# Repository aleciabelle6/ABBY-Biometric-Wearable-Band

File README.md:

# Anxiety Buddy Band for Youth (ABBY) - Biometric Wearable Band  
_Alecia Barbieri — Princeton University ECE Funded Summer Internship, 2023_

## Project Overview

This repository contains the KiCad design files for a custom Electrodermal Activity (EDA) and heart rate/blood oxygen sensor signal conditioning circuit. It integrates analog signal conditioning stages to filter, amplify, and prepare the weak physiological signals from wearable electrodes and sensors for digitization. This project involved extending and enhancing the Open-Smartwatch-Light open-source platform (https://open-smartwatch.github.io/) by advancing its electronic hardware and serves as my first exposure to KiCAD. 

The circuit is designed to amplify and clean signals from EDA electrodes, with additional capability for heart rate and blood oxygen sensing and position tracking. The design focuses on maximizing signal fidelity through multi-stage amplification and filtering, using a low-power LM324D operational amplifier.

---

## Circuit Extension Design Summary

Taking on this project with no prior experience in PCB design was a very daunting but nonetheless rewarding endeavor. As such, I gained so much knowledge from starting with an open-source PCB layout and extending the functionality of it. Below, I describe the various additions that I made to the design.

### Heart rate and Pulse Sensing

The BH1792GLC-E2 is an optical sensor that measures heart rate and pulse by detecting changes in blood volume using reflected green light. It emits green light through integrated LEDs and captures the reflected signal from skin tissue using a photodiode. This reflected light varies with blood flow, allowing the sensor to extract photoplethysmography (PPG) pulse wave information that is digitized internally and outputt via I2C to the ESP32 microcontroller. The sensor operates with precise timing control and built-in ambient light cancellation for the purpose of enhancing signal quality and reducing noise.

### EDA Sensor Signal Processing

EDA (Electrodermal Activity) electrodes measure changes in skin conductance caused by sweat gland activity, which reflects stress levels. I designed an analog signal conditioning chain that consists of three distinct stages, each implemented using one of the four internal amplifiers in the LM324D quad op-amp IC, for the purpose of having access to noise-free, clear, and useful data that can inform the microcontroller on parts of the physiological makeup that even the user isn't aren't aware of. The raw EDA signal interfaces with the board through an SJ-3524 connector. From there it gets processed through a 3-stage amplifier. The first stage is a differential amplifier stage, which takes in the raw EDA electrode signals, biased with a 1.65 V reference to accommodate single-supply operation and amplifies the differential signal from the electrodes while rejecting common-mode noise and interference. The second stage is an active low-pass filter stage which attenuates high-frequency noise and artifacts, preserving the low-frequency physiological signals typical in EDA and heart rate sensing. The third and final stage is the gain stage, which provides a gain of 11 to bring the signal into an optimal range for analog-to-digital conversion. This conditioned final signal then gets sent to an ADC input that then interfaces with the I2C protocols of the ESP32 at address 0x48.  

### Miscellaneous Changes
I changed the circular Open-Smartwatch-Light into a rectangular board to have enough room to accommodate the new devices. With this, I rerouted the entire board, prioritizing sectioning off analog, digital, and power lines as much as possible with the limited board space and also prioritized having sufficient trace width for the current passing through each branch of the circuit. 

---

## Circuit Component Overview

This section highlights the different components' functions in the circuit as visually depicted in the image below.

The TTGO T-Micro32 V2.0 (ESP32-based Microcontroller) was used due to its very compact size, coming in at 45% smaller than standard ESP32. It has full GPIO support, Wi-Fi and Bluetooth features, and advanced power-saving features including clock gating, deep sleep, and dynamic power delegation. This microcontroller controls all of the devices, primarily using I2C to communicate with the different sensors as well as the ADC converter.

As far as sensing, the BH1792GLC-E2 ECG/PPG Heart Rate and Oximeter Sensor is an IR-based pulse wave sensor for heart rate and SpO2 monitoring. Communicates via I2C, uses interrupt-based burst reads, and includes bypass capacitors for power stability. The BMA400 3-axis accelerometer is an ultra-low power accelerometer for motion and activity tracking. It integrates with I2C, uses INT pin for data-ready alerts, and includes bypass capacitor for voltage filtering. The board supports an external pair of EDA electrodes spaced 4 cm apart at the top and bottom of the wrist for optimal skin conductance sensing. They are routed through SJ-3524 connector, then through 3-stage amplifier, then through ADC, then to I2C. In order for the EDA electrodes to be able to interface with the rest of the electronics, it must have a SJ-3524-SMT connector jack as seen in this pair of EDA electrodes: https://lafayettepolygraph.com/products/eda-assembly-7ft-lx6/. Throughout the board there are many capacitors used for voltage stability, filtering, and transient suppression across biosensors, power supply, and signal lines. Resistors are also employed in various places for pulling up the I2C lines as well as noise cancelling, as seen in the low pass filter for the EDA electrode signals.

The GC9A01 IPS Display: 1.28” circular IPS LCD with SPI interface, parallel RGB support, and adjustable brightness via 2N7002 transistor switch, which happenss by adjusting current through the LEDK pin on the GC9A01 screen, which in turn adjusts the backllight brightness of the display. This display screen offers wide viewing angles and vibrant display quality. There are also 3 SPST Buttons used for power enable (EN pin control) and general-purpose user inputs (e.g. calibrate, transmit).

The power delegation of the board is quite intuitive. The board is powered by a 3.7V LiPo battery with shorting protection; monitored via voltage divider and B_MON pin for on-screen battery status display. The MCP73831 LiPo Charging Management Controller is a constant-current/voltage charger with thermal regulation, charge termination, and USB-powered battery input for safe, efficient battery management. The TPS2115A Power Multiplexer is a smart autoswitching between USB and battery power sources based on availability and voltage conditions. It acts very similiar to a rely in that it relies on the battery level of the battery to determine which input to transfer to the output and to the next stage of the power management system. The PCB also contains 2 XC6209 LDO Voltage regulators that convert the output of the multiplexer to a consistent 3.3V output regardless of the input level, allowing for consistent operation of sensor powering and the main logic throughout the circuit. The micro-USB port has two functions as it takes in a charging cable to charge the onboard Li-Po battery using a regulated charging circuit, and this port also provides a data interface for uploading firmware to the microcontroller. This enables both power management and programming through a single, convenient connection. With this, the CH340E chip is a USB to Serial Converter converts the inputs of the micro-USB to UART to connect with the microcontroller to upload firmware. 

---

## PCB Circuit Layout Images

Below is the 3D circuit layout of the board followed by the front and back viewport as well as a 3D isometric viewport. As seen from the images below, the front of the board hosts the sensors, processors, buttons, external wire inputs, and passive components that sit on the side of the wrist in order to allow for the heart rate/pulse sensor to be able to better interface with the wrist. The back of the PCB contains the interfaces for the screen display and the external 3.7 LiPo battery, which is hosted below the screen but above the PCB.

---

## Repository Contents

- **KiCad Project Files:** Schematic, PCB layout, and BOM files for the full EDA signal conditioning circuit.
- **EDA Models:** The symbol, footprint, and 3D CAD model for each component on the PCB.
- **Datasheets:** Relevant datasheets for each component.

## Getting Started

1. Clone the repository:
   ```bash
   git clone https://github.com/aleciabelle6/ABBY-Biometric-Wearable-Band.git
   cd ABBY-Biometric-Wearable-Band
2. On KiCAD, select **File > Open Project**.
3. Navigate to where you cloned this repository and open the file *abbyWatchV1.kicad_pro*. 

## License

This project is made available for academic, non-commercial use. Please contact me if you'd like to use any part of the content or code beyond that scope.

---
*Author: Alecia Barbieri ([LinkedIn](https://www.linkedin.com/in/aleciabarbieri))*  
*Project Advisor: Dr. David Wentzlaff*  
*Department of Electrical and Computer Engineering, Princeton University*

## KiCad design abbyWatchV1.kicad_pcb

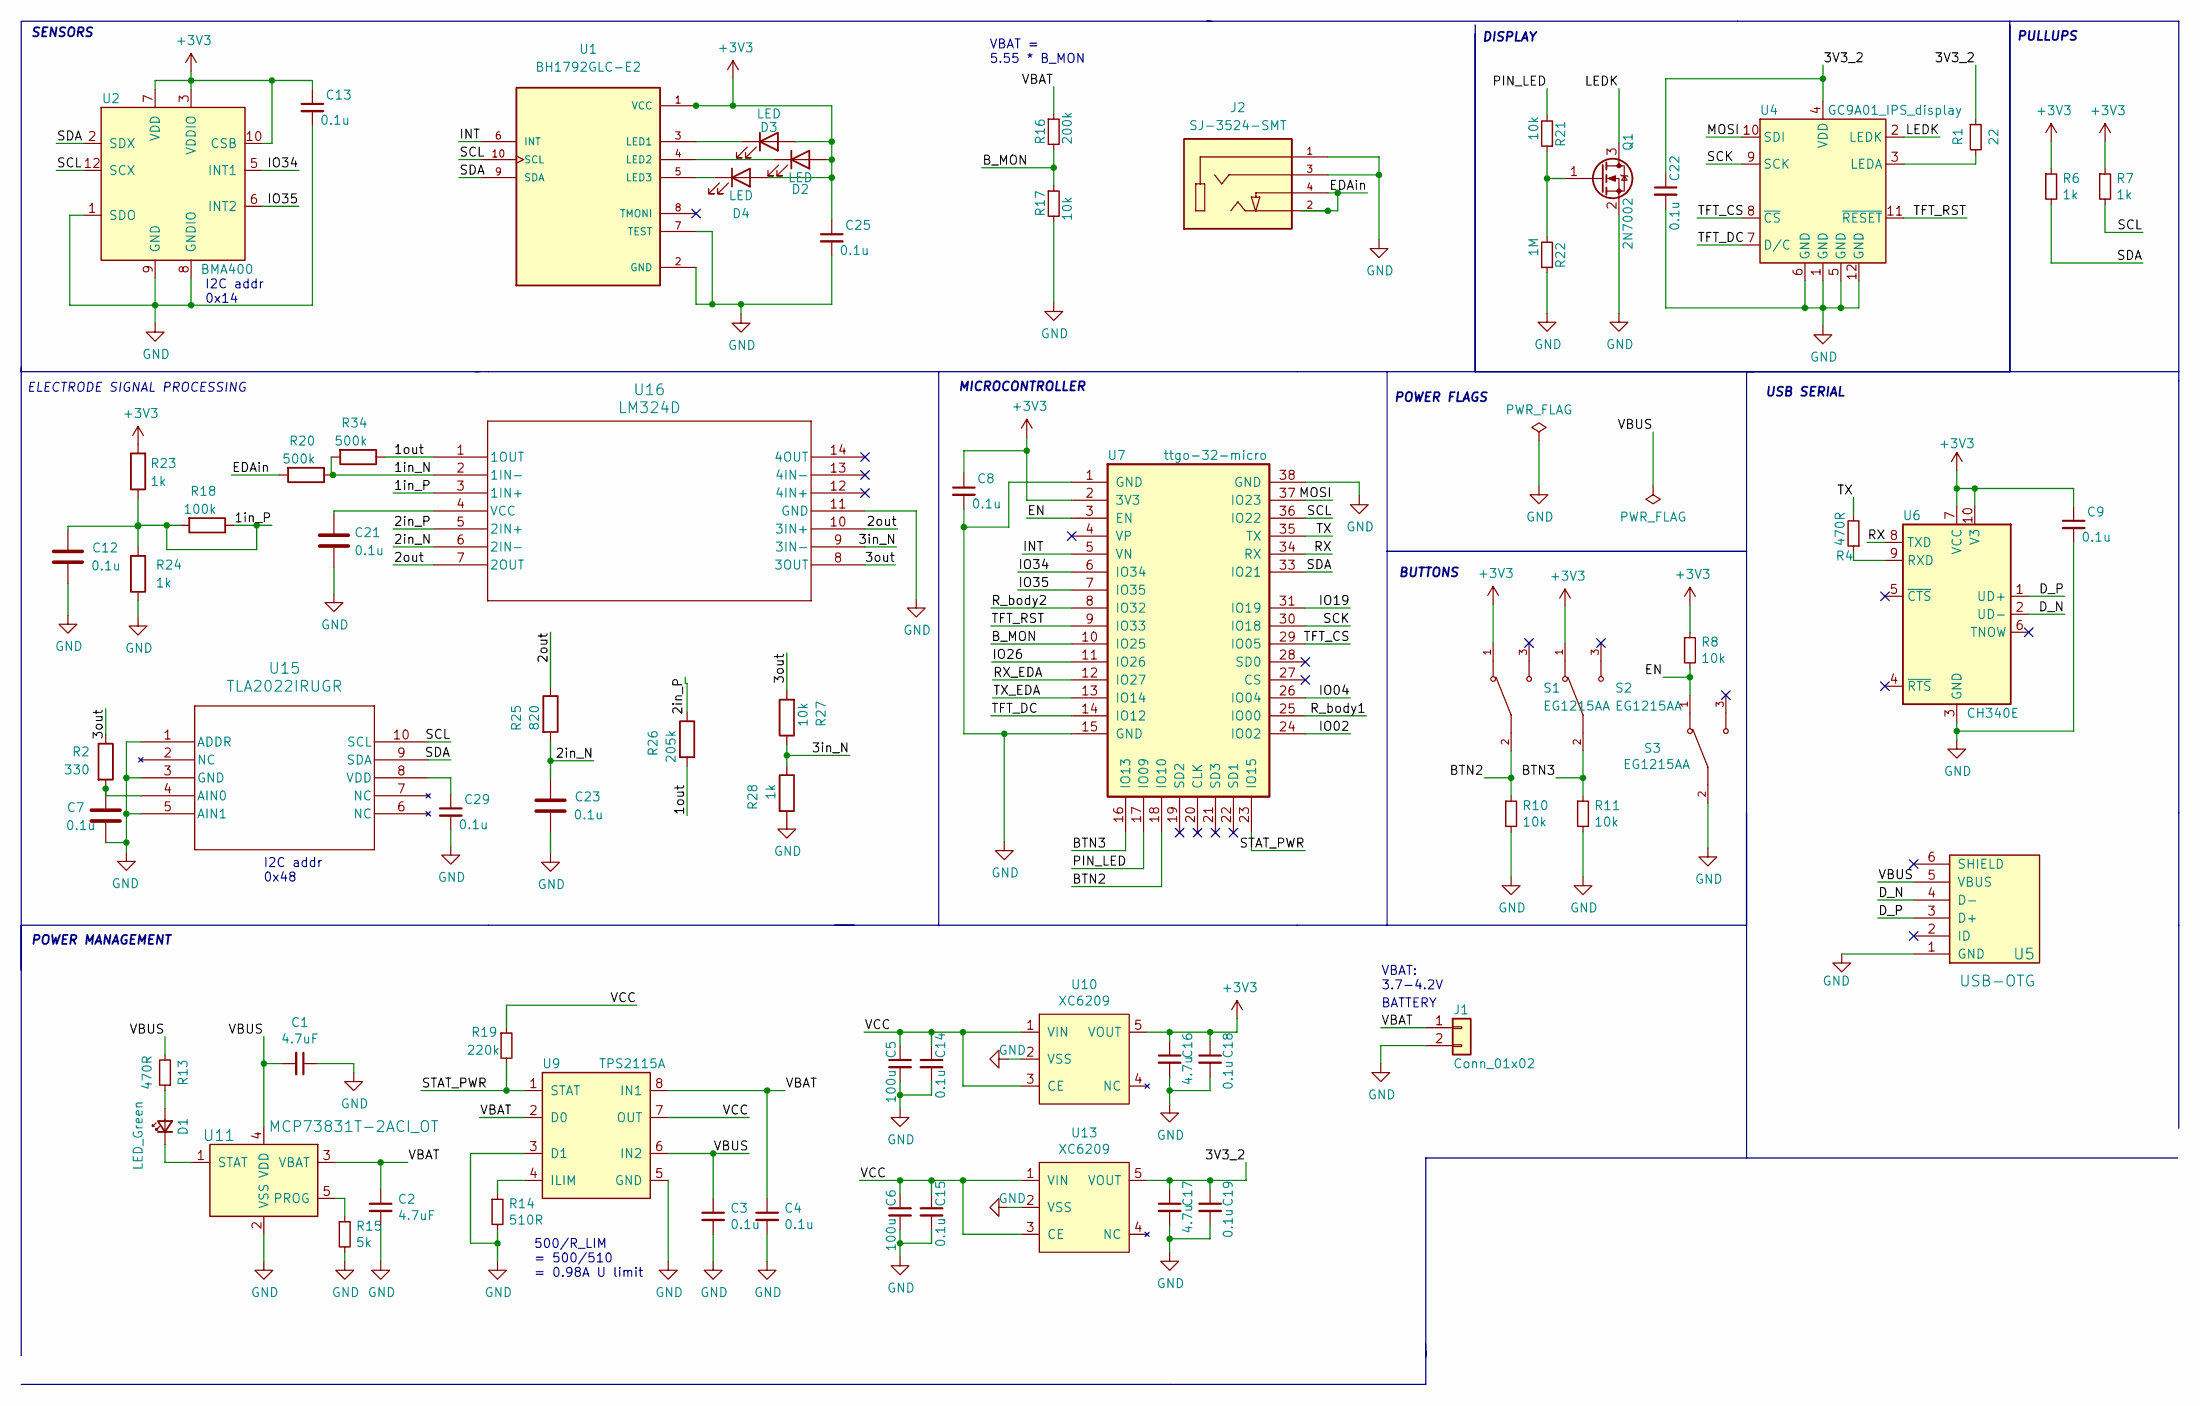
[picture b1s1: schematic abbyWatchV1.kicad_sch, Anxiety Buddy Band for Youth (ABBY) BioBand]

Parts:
C1, C2: 4.7uF; C_0603_1608Metric
C3, C4, C7, C8, C9, C12, C13, C14, C15, C18, C19, C21, C22, C23, C25, C29: 0.1u; C_0603_1608Metric
C5, C6: 100u; C_1206_3216Metric
C16, C17: 4.7u; C_0603_1608Metric
D1: LED_Green; LED_0805_2012Metric
D2, D3, D4: LED; LED_1206_3216Metric
J1: Conn_01x02; PinHeader_1x02_P2.54mm_Vertical
J2: SJ-3524-SMT; CUI_SJ-3524-SMT; PARTREV 1.03
Q1: 2N7002; SOT-23
R1: 22; R_0603_1608Metric
R2: 330; R_0603_1608Metric
R4, R13: 470R; R_0603_1608Metric
R6, R7, R23, R24, R28: 1k; R_0603_1608Metric
R8, R10, R11, R17, R21, R27: 10k; R_0603_1608Metric
R14: 510R; R_0603_1608Metric
R15: 5k; R_0603_1608Metric
R16: 200k; R_0603_1608Metric
R18: 100k; R_0603_1608Metric
R19: 220k; R_0603_1608Metric
R20, R34: 500k; R_0603_1608Metric
R22: 1M; R_0603_1608Metric
R25: 820; R_0603_1608Metric
R26: 205k; R_0603_1608Metric
S1, S2, S3: EG1215AA; CONN3_3033816_WRE; PARTREV A
U1: BH1792GLC-E2; XDCR_BH1792GLC-E2; PARTREV 002
U2: BMA400; narrow0.19mmV2BMA400; MPN BMA400; DigiKey_PN 828-1081-1-ND
U4: GC9A01_IPS_display
U5: USB-OTG; USBmicro-B
U6: CH340E; MSOP-10_3x3mm_P0.5mm
U7: ttgo-32-micro
U9: TPS2115A; TSSOP-8_4.4x3mm_P0.65mm; MPN TPS2115APWR; DigiKey_PN 296-16940-1-ND
U10, U13: XC6209; SOT-23-5
U11: MCP73831T-2ACI_OT; SOT-23-5; MPN MCP73831T-2ACI/OT; Digi-Key_PN MCP73831T-2ACI/OTCT-ND
U15: TLA2022IRUGR; RUG10_TEX
U16: LM324D; D14

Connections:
+3V3: C8.1, C9.1, C13.1, C16.1, C18.1, C25.1, D2.2 (A), D3.2 (A), D4.2 (A), R6.1, R7.1, R8.1, R23.2, S1.1, S2.1, U1.1 (VCC), U2.3 (VDDIO), U2.7 (VDD), U2.10 (CSB), U6.7 (VCC), U6.10 (V3), U7.2 (3V3), U10.5 (VOUT)
/1in_N: R20.1, R34.2, U16.2 (1IN-)
/1in_P: C12.1, R18.1, R18.2, R23.1, R24.2, U16.3 (1IN+)
/1out: R26.2, R34.1, U16.1 (1OUT)
/2in_N: C23.1, R25.2, U16.6 (2IN-)
/2in_P: R26.1, U16.5 (2IN+)
/2out: R25.1, U16.7 (2OUT), U16.10 (3IN+)
/3V3_2: C17.1, C19.1, C22.1, R1.1, U4.4 (VDD), U13.5 (VOUT)
/3in_N: R27.1, R28.1, U16.9 (3IN-)
/3out: R2.1, R27.2, U16.8 (3OUT)
/BTN2: R10.1, S1.2, U7.18 (IO10)
/BTN3: R11.1, S2.2, U7.16 (IO13)
/B_MON: R16.2, R17.1, U7.10 (IO25)
/D_N: U5.4 (D-), U6.2 (UD-)
/D_P: U5.3 (D+), U6.1 (UD+)
/EDAin: J2.2, J2.4, R20.2
/EN: R8.2, S3.1, U7.3 (EN)
/INT: U1.6 (INT), U7.5 (VN)
/IO02: U7.24 (IO02)
/IO04: U7.26 (IO04)
/IO19: U7.31 (IO19)
/IO26: U7.11 (IO26)
/IO34: U2.5 (INT1), U7.6 (IO34)
/IO35: U2.6 (INT2), U7.7 (IO35)
/LEDK: Q1.3 (D), U4.2 (LEDK)
/MOSI: U4.10 (SDI), U7.37 (IO23)
/PIN_LED: R21.2, U7.17 (IO09)
/RX: U6.8 (TXD), U7.34 (RX)
/RX_EDA: U7.12 (IO27)
/R_body1: U7.25 (IO00)
/R_body2: U7.8 (IO32)
/SCK: U4.9 (SCK), U7.30 (IO18)
/SCL: R7.2, U1.10 (SCL), U2.12 (SCX), U7.36 (IO22), U15.10 (SCL)
/SDA: R6.2, U1.9 (SDA), U2.2 (SDX), U7.33 (IO21), U15.9 (SDA)
/STAT_PWR: R19.2, U7.23 (IO15), U9.1 (STAT)
/TFT_CS: U4.8 (~CS), U7.29 (IO05)
/TFT_DC: U4.7 (D/C), U7.14 (IO12)
/TFT_RST: U4.11 (~RESET), U7.9 (IO33)
/TX: R4.2, U7.35 (TX)
/TX_EDA: U7.13 (IO14)
/VBAT: C2.1, C4.1, J1.1, R16.1, U9.2 (D0), U9.8 (IN1), U11.3 (VBAT)
/VBUS: C1.2, C3.1, R13.2, U5.5 (VBUS), U9.6 (IN2), U11.4 (VDD)
/VCC: C5.1, C6.1, C14.1, C15.1, R19.1, U9.7 (OUT), U10.1 (VIN), U10.3 (CE), U13.1 (VIN), U13.3 (CE)
GND: C1.1, C2.2, C3.2, C4.2, C5.2, C6.2, C7.2, C8.2, C9.2, C12.2, C13.2, C14.2, C15.2, C16.2, C17.2, C18.2, C19.2, C21.2, C22.2, C23.2, C25.2, C29.2, J1.2, J2.1, J2.3, Q1.2 (S), R10.2, R11.2, R14.2, R15.2, R17.2, R22.1, R24.1, R28.2, S3.2, U1.2 (GND), U1.7 (TEST), U2.1 (SDO), U2.8 (GNDIO), U2.9 (GND), U4.1 (GND), U4.5 (GND), U4.6 (GND), U4.12 (GND), U5.1 (GND), U6.3 (GND), U7.1 (GND), U7.15 (GND), U7.38 (GND), U9.3 (D1), U9.5 (GND), U10.2 (VSS), U11.2 (VSS), U13.2 (VSS), U15.1 (ADDR), U15.3 (GND), U15.5 (AIN1), U16.11 (GND)
unnamed: D1.2 (A), R13.1
unnamed: D1.1 (K), U11.1 (STAT)
unnamed: D2.1 (K), U1.4 (LED2)
unnamed: D3.1 (K), U1.3 (LED1)
unnamed: D4.1 (K), U1.5 (LED3)
unnamed: Q1.1 (G), R21.1, R22.2
unnamed: R1.2, U4.3 (LEDA)
unnamed: R4.1, U6.9 (RXD)
unnamed: R14.1, U9.4 (ILIM)
unnamed: R15.1, U11.5 (PROG)
unnamed: C7.1, R2.2, U15.4 (AIN0)
unnamed: C29.1, U15.8 (VDD)
unnamed: C21.1, U16.4 (VCC)

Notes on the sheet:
500/R_LIM = 500/510 = 0.98A U limit
VBAT = 5.55 * B_MON
I2C addr 0x14
SENSORS
POWER FLAGS
PULLUPS
ELECTRODE SIGNAL PROCESSING
BATTERY
USB SERIAL
BUTTONS
VBAT: 3.7-4.2V
MICROCONTROLLER
POWER MANAGEMENT
I2C addr 0x48
DISPLAY

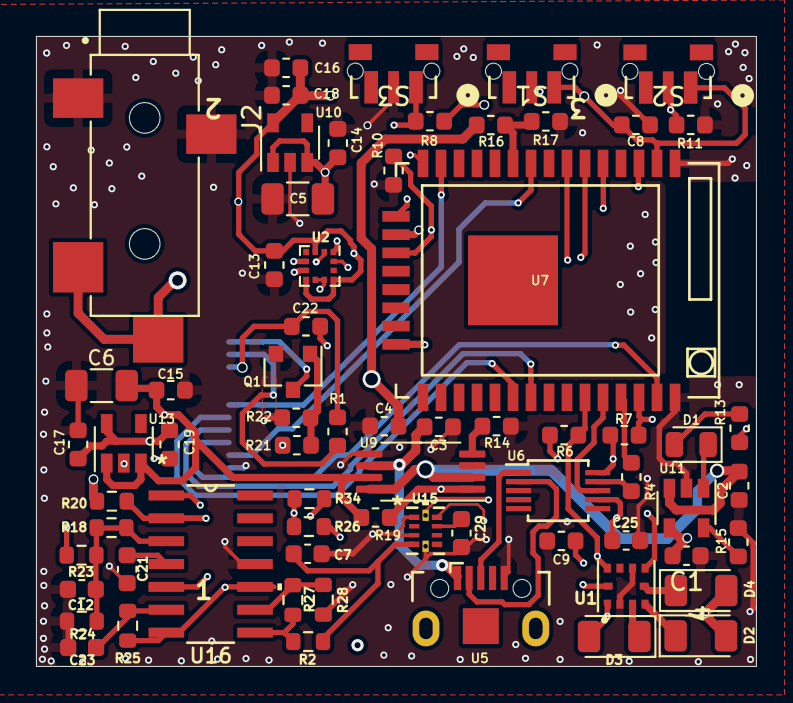
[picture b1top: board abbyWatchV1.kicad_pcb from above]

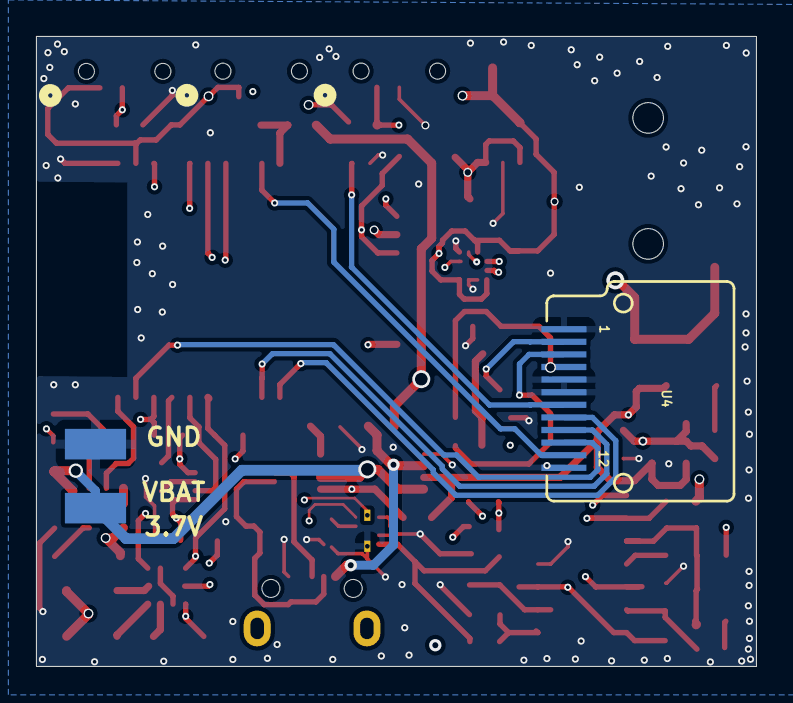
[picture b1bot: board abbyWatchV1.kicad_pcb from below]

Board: 4 copper layers, 40.0 x 35.0 mm, 69 parts (2 on the bottom side), 49 nets.

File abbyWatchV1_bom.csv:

Tool:,Eeschema 7.0.9,,,,,,,
Generator:,C:\Users\aleci\OneDrive\bin\scripting\plugins/bom_csv_grouped_by_value.py,,,,,,,
Component Count:,69,,,,,,,
,,,,,,,,
Collated Components:,,,,,,,,
,,,,,,,,
Item,Qty,Reference(s),Value,LibPart,Footprint,Datasheet,MPN,Manufacturer
1,2,"C1, C2",4.7uF,Device:C_Small,Capacitor_SMD:C_0603_1608Metric,General,General,General
2,12,"C3, C4, C8, C9, C13, C14, C15, C18, C19, C22, C25, C29",0.1u,Device:C_Small,Capacitor_SMD:C_0603_1608Metric,General,General,General
3,2,"C5, C6",100u,Device:C_Small,Capacitor_SMD:C_1206_3216Metric,General,General,General
4,4,"C7, C12, C21, C23",0.1u,Device:C,Capacitor_SMD:C_0603_1608Metric,General,General,General
5,2,"C16, C17",4.7u,Device:C_Small,Capacitor_SMD:C_0603_1608Metric,General,General,General
6,1,D1,LED_Green,Device:LED_Small,LED_SMD:LED_0805_2012Metric,General,General,General
7,3,"D2, D3, D4",LED,Device:LED,LED_SMD:LED_1206_3216Metric,General,General,General
8,1,J1,Conn_01x02,Connector_Generic:Conn_01x02,Connector_PinHeader_2.54mm:PinHeader_1x02_P2.54mm_Vertical,General,General,General
9,1,J2,SJ-3524-SMT,SJ3524:SJ-3524-SMT,SJ3524:CUI_SJ-3524-SMT,https://www.sameskydevices.com/product/resource/sj-352x-smt.pdf,SJ-352X-SMT,same sky
10,1,Q1,2N7002,Transistor_FET:2N7002,Package_TO_SOT_SMD:SOT-23,https://www.fairchildsemi.com/datasheets/2N/2N7002.pdf,,onsemi
11,1,R1,22,Device:R_Small,Resistor_SMD:R_0603_1608Metric,General,General,General
12,1,R2,330,Device:R,Resistor_SMD:R_0603_1608Metric,General,General,General
13,2,"R4, R13",470R,Device:R_Small,Resistor_SMD:R_0603_1608Metric,General,General,General
14,2,"R6, R7",1k,Device:R_Small,Resistor_SMD:R_0603_1608Metric,General,General,General
15,5,"R8, R10, R11, R17, R21",10k,Device:R_Small,Resistor_SMD:R_0603_1608Metric,General,General,General
16,1,R14,510R,Device:R_Small,Resistor_SMD:R_0603_1608Metric,General,General,General
17,1,R15,5k,Device:R_Small,Resistor_SMD:R_0603_1608Metric,General,General,General
18,1,R16,200k,Device:R_Small,Resistor_SMD:R_0603_1608Metric,General,General,General
19,1,R18,100k,Device:R,Resistor_SMD:R_0603_1608Metric,General,General,General
20,1,R19,220k,Device:R_Small,Resistor_SMD:R_0603_1608Metric,General,General,General
21,2,"R20, R34",500k,Device:R,Resistor_SMD:R_0603_1608Metric,General,General,General
22,1,R22,1M,Device:R_Small,Resistor_SMD:R_0603_1608Metric,General,General,General
23,3,"R23, R24, R28",1k,Device:R,Resistor_SMD:R_0603_1608Metric,General,General,General
24,1,R25,820,Device:R,Resistor_SMD:R_0603_1608Metric,General,General,General
25,1,R26,205k,Device:R,Resistor_SMD:R_0603_1608Metric,General,General,General
26,1,R27,10k,Device:R,Resistor_SMD:R_0603_1608Metric,General,General,General
27,3,"S1, S2, S3",EG1215AA,switches:EG1215AA,buttons:CONN3_3033816_WRE,https://configured-product-images.s3.amazonaws.com/Datasheet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,EG1215AA,E-Switch
28,1,U1,BH1792GLC-E2,pulse:BH1792GLC-E2,pulse:XDCR_BH1792GLC-E2,https://fscdn.rohm.com/en/products/databook/datasheet/ic/sen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,BH1792GLC,Rohm Semiconductor
29,1,U2,BMA400,open-Smartwatch:BMA400,open-Smartwatch:narrow0.19mmV2BMA400,https://ae-bst.resource.bosch.com/media/_tech/media/datashee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,BMA400,Bosch Sensortec
30,1,U4,GC9A01_IPS_display,open-Smartwatch:GC9A01_IPS_display_SPI,open-Smartwatch:GC9A01_IPS_display,https://www.buydisplay.com/download/ic/GC9A01A.pdf?srsltid=A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,GC9A01A,GalaxyCore
31,1,U5,USB-OTG,open-Smartwatch:USB-OTG,open-Smartwatch:USBmicro-B,https://www.ti.com/lit/ml/sprp605/sprp605.pdf,General,General
32,1,U6,CH340E,open-Smartwatch:CH340E,open-Smartwatch:MSOP-10_3x3mm_P0.5mm,https://www.mpja.com/download/35227cpdata.pdf,,
33,1,U7,ttgo-32-micro,open-Smartwatch:ttgo-32-micro,open-Smartwatch:ttgo-32-micro,https://github.com/LilyGO/TTGO-Micro32-V2.0/blob/master/Data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,TTGO Micro?32 V2.0,LILYGO
34,1,U9,TPS2115A,open-Smartwatch:TPS2115A_default,open-Smartwatch:TSSOP-8_4.4x3mm_P0.65mm,https://www.ti.com/lit/ds/symlink/tps2114a.pdf?HQS=TI-null-n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,TPS2115APWR,Texas Instruments
35,2,"U10, U13",XC6209,open-Smartwatch:XC6209,Package_TO_SOT_SMD:SOT-23-5,https://product.torexsemi.com/system/files/series/xc6209.pdf,XC6209,Torex Semiconductors Ltd.
36,1,U11,MCP73831T-2ACI_OT,open-Smartwatch:MCP73831T-2ACI_OT,open-Smartwatch:SOT-23-5,https://www.digikey.com/en/products/detail/microchip-technol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,MCP73831T-2ACI/OT,Microchip Technology
37,1,U15,TLA2022IRUGR,TLA2022:TLA2022IRUGR,TLA2022:RUG10_TEX,https://www.ti.com/lit/gpn/tla2022,TLA2022IRUGR,Texas Instruments
38,1,U16,LM324D,LM324:LM324D,LM324D:D14,https://www.ti.com/lit/gpn/lm324,LM324D,Texas Instruments

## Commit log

2025-07-28 Initial Commit: uploading all files
2025-07-31 Added project images and all component CAD models
2025-08-01 Update README.md
    Added project images, including visuals of the circuit schematic, 3D board layout, and front, back, and isometric viewports.
